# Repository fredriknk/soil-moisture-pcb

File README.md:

Further work on https://github.com/fredriknk/SoilSense

# soil-moisture-pcb
Capacitive soil moisture sensor routed in KiCad. Uses an Fastnel NRF52840 module, and is powered by a 3.0v coin cell battery.

## PCB Layout

| Front Copper                           | Back Copper |
| ----------------------------------------- | -----
|  |  |

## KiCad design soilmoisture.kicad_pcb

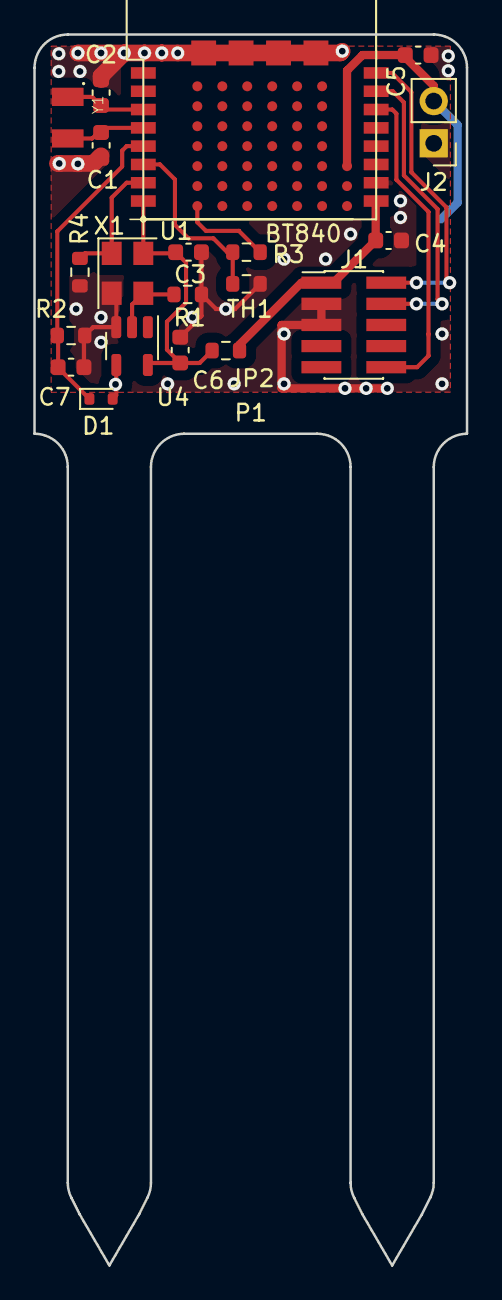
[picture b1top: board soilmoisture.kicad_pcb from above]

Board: 4 copper layers, 26.0 x 74.0 mm, 22 parts (1 on the bottom side), 15 nets.

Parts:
C1, C2: 12pF; C_0603_1608Metric
C3, C6, C7: 100nF; C_0603_1608Metric
C4, C5: 4.7uf; C_0603_1608Metric
D1: CDSU101A; D_SOD-523
J1: Conn_ARM_JTAG_SWD_10; PinHeader_2x05_P1.27mm_Vertical_SMD
J2: Conn_01x02; PinHeader_1x02_P2.54mm_Vertical
JP2: 0R; R_0603_1608Metric
P1: 1-30pf; 1-30pf_Soil_Probe
R1, R2, R3, R4: 100k; R_0603_1608Metric
TH1: Thermistor_NTC; R_0603_1608Metric
U1: BT840; BT840-BT840
U2: BAT-HLD-001
U4: SN74LVC1G14DBV; SOT-23-5
X1: SIT8008BC-23-18E-80.000000; Oscillator_SMD_SeikoEpson_SG8002CE-4Pin_3.2x2.5mm
Y1: ABS07-32.768KHZ-T; XTAL320X150X90

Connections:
+BATT: C5.1, J2.2, U1.P$F4 (F4/VDDH), U2.+@2
/NTC_POWER: R3.1, U1.P$Z6 (Z6/P106)
/Oscillator/ADC_OUT: C7.1, D1.1 (K), R2.1, U1.P$5 (P02/AIN0)
/Oscillator/Probe: D1.2 (A), P1.1, U4.4
/Oscillator/enable: R4.1, U1.P$7 (P09), X1.1 (EN)
/Oscillator/gpio_power: C3.1, C6.1, JP2.1 (A), U1.P$8 (P10), U4.5 (VCC), X1.4 (Vdd)
/SWDCLK: J1.4 (SWDCLK/TCK), U1.P$15 (SWCLK)
/SWDIO: J1.2 (SWDIO/TMS), U1.P$16 (SWDIO)
/XL1: C2.2, U1.P$3 (P00/XL1), Y1.1
/XL2: C1.2, U1.P$4 (P01/XL2), Y1.2
/nRST: J1.10 (~RESET), U1.P$14 (P21/RESET)
GND: C1.1, C2.1, C3.2, C4.2, C5.2, C6.2, C7.2, J1.3 (GND), J1.5 (GND), J2.1, P1.2, R1.2, R2.2, R4.2, TH1.2, U1.P$10 (GND), U1.P$F0 (F0/GND), U1.P$F1 (F1/GND), U1.P$F2 (F2/GND), U1.P$F3 (F3/GND), U2.-, U4.3 (GND), X1.2 (GND)
NTC_ADC: R3.2, TH1.1, U1.P$6 (P03/AIN1)
unnamed: R1.1, U4.2, X1.3 (OUT)
VDD: C4.1, J1.1 (VCC), JP2.2 (B), U1.P$9 (VDD)

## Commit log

2023-03-28 Feat: Four layer pcb, added NTC
2023-03-29 Feat: Memsic oscillator and schmitt buffer, dual probes
